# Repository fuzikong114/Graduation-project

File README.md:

# Graduation-project

毕业设计项目的硬件资料。

## 项目列表

| 目录 | 说明 | 状态 |
|---|---|---|
| [`hardware/stm32-environment-monitor`](hardware/stm32-environment-monitor) | **基于 STM32 的多功能环境智能监控系统**：温湿度、光照、RTC、OLED、按键、LED、蜂鸣器、12V 灯带控制，12V 输入板载降压 | V1.2，已提交嘉立创打样 |
| [`hardware/parking-bluepill`](hardware/parking-bluepill) | **4 车位检测板**：Blue Pill 核心板 + 4 个红外反射传感器 + OLED（KiCad 工程） | `main` 为初版；**更新版在分支 [`claude/blissful-cannon-at318t`](../../tree/claude/blissful-cannon-at318t)**（尚未合并） |

## 环境监控板（V1.2）简介

- 主控：立创·地阔星 STM32F103C8T6 开发板，插在 2×20 排母上。
- 传感与显示：GXHT30C 温湿度、SD3077 实时时钟（CR1220 备份电池）、0.96" OLED（4P 母座）、光敏电阻。
- 输出：有源蜂鸣器、红/绿/黄 LED、12V LED 灯带（AO3400A 开关）。
- 输入：4 个按键（PA0~PA3）。
- 供电：12V DC 座 → 保险丝 → XL1509 降压到 5V；3.3V 由开发板 LDO 提供。
- 下载程序：开发板自带 SWD 口，接 DAP-Link；Type-C 只供电。

更多内容（引脚表、BOM、Gerber、装配注意事项）见
[环境监控板 README](hardware/stm32-environment-monitor/README.md)，
原理图见 [`docs/原理图.png`](hardware/stm32-environment-monitor/docs/原理图.png)。

## 车位检测板的更新版

更新版（2026-11-12）在分支 `claude/blissful-cannon-at318t`，`main` 上还是旧版。主要改动：

- 核心板改为 GD32F103C8T6 Type-C 核心板（引脚与 Blue Pill 兼容）。
- 传感器由 VCNT2030 改为 XL-ITR8307（成兴光，现货，引脚外露好焊）。
- 修正 OLED 引脚顺序，加去耦电容和 GND 铺铜，附嘉立创 SMT 的 BOM。
- PCB 文件改为 KiCad 9 格式，方便导入嘉立创 EDA。

详细说明见该分支的 `hardware/parking-bluepill/CHANGES.md`。

## 工具

- 环境监控板：嘉立创 EDA 专业版（`.epro`）
- 车位检测板：KiCad

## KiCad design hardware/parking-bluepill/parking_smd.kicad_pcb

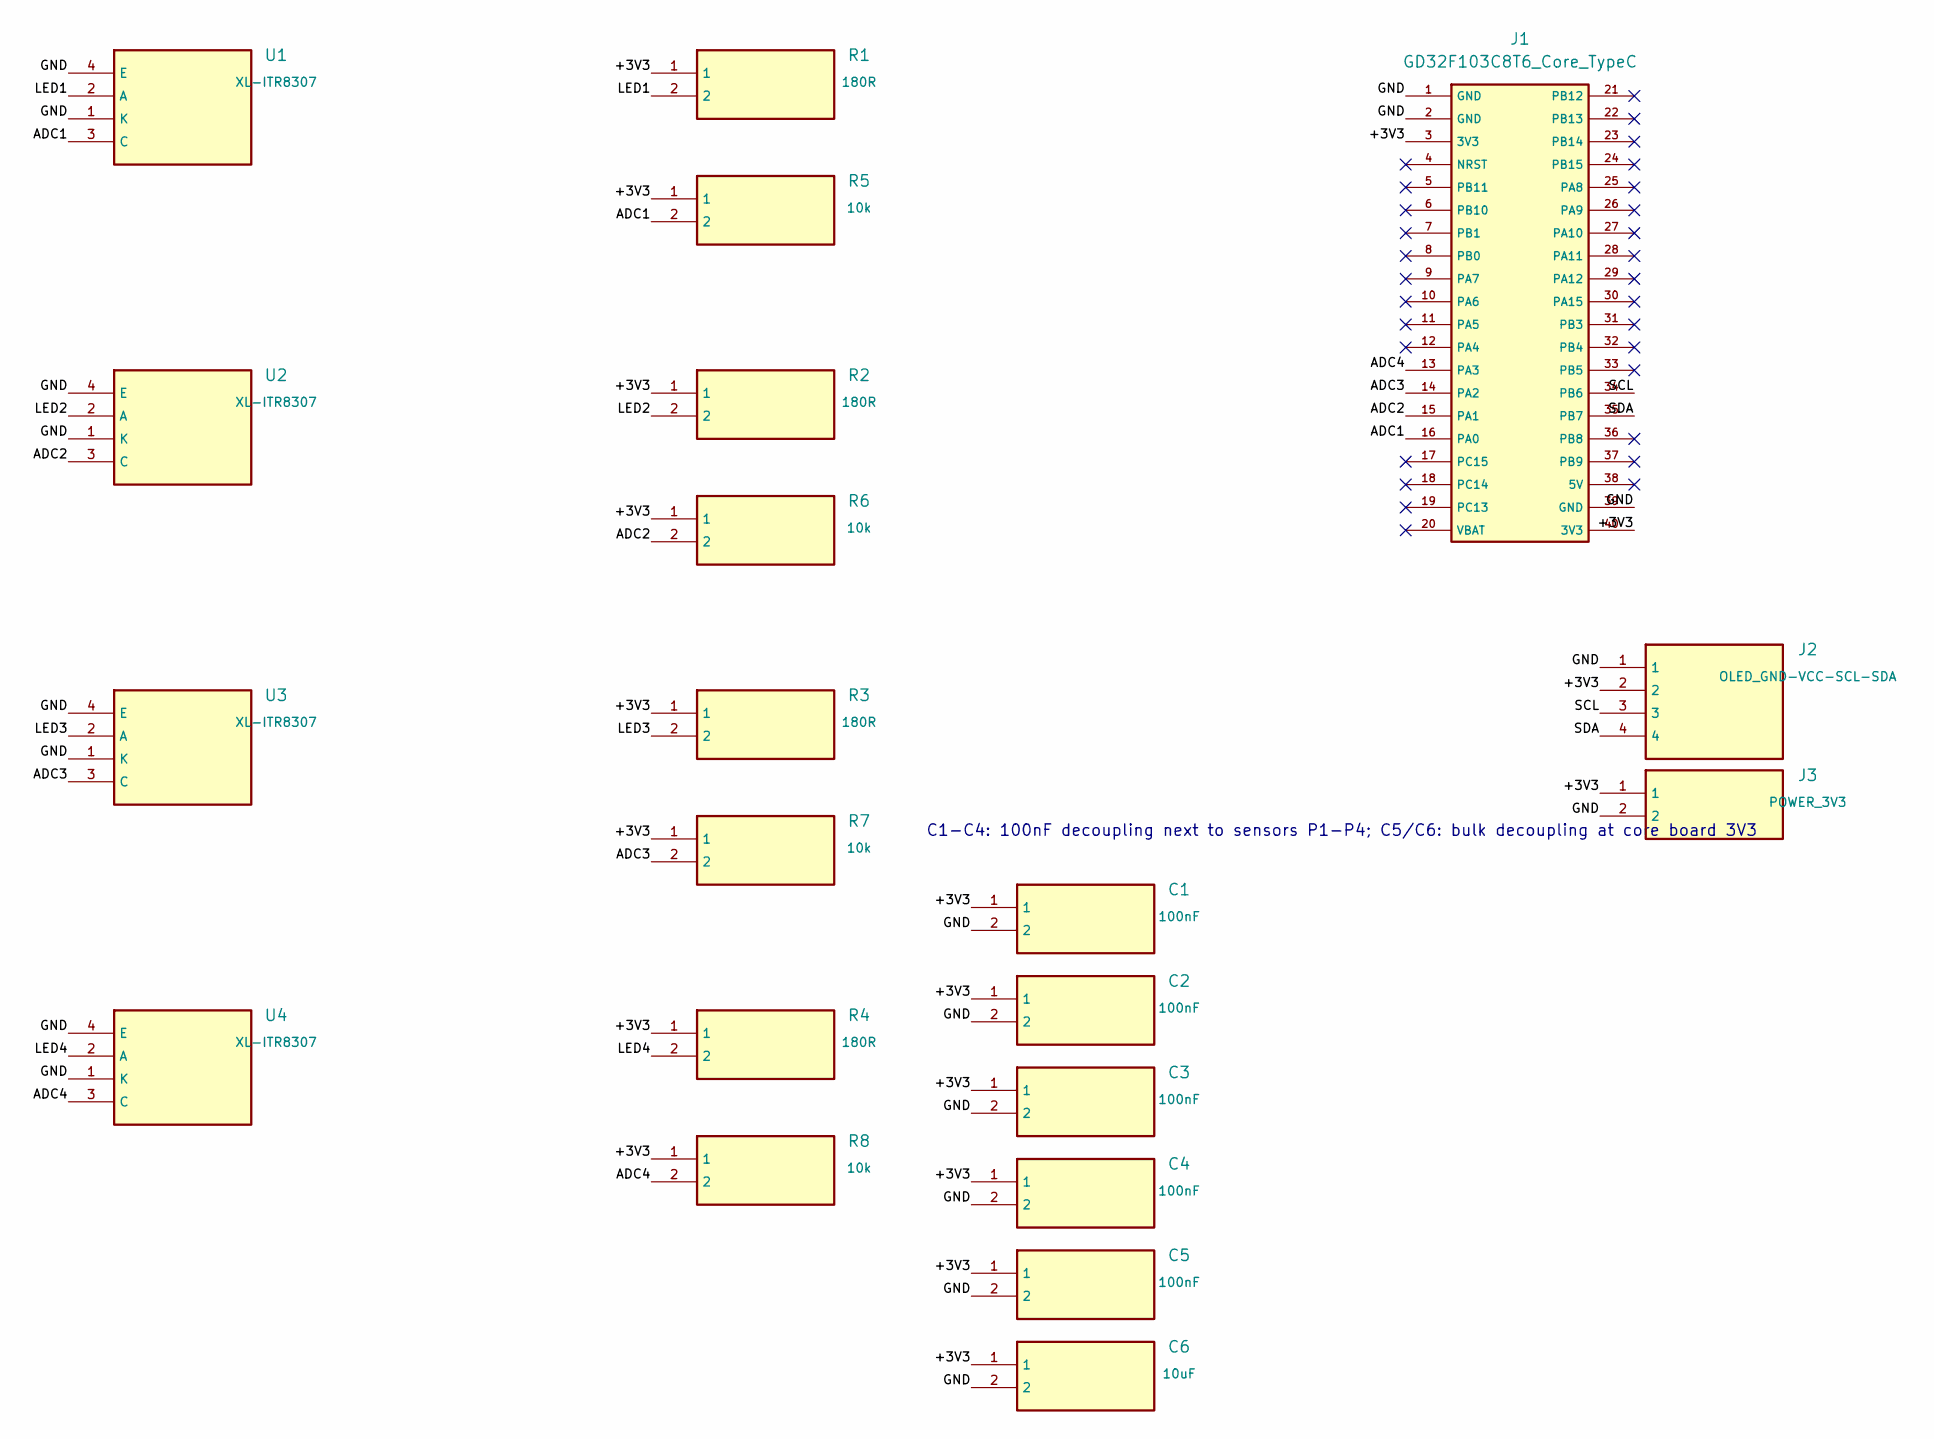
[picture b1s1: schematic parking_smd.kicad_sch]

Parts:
C1, C2, C3, C4, C5: 100nF; C_0805_2012Metric; LCSC C49678
C6: 10uF; C_0805_2012Metric; LCSC C15850
J1: GD32F103C8T6_Core_TypeC; BluePill_2x20_P2.54_Row15.24
J2: OLED_GND-VCC-SCL-SDA; PinHeader_1x04_P2.54mm_Vertical
J3: POWER_3V3; PinHeader_1x02_P2.54mm_Vertical
R1, R2, R3, R4: 180R; R_0805_2012Metric; LCSC C25270
R5, R6, R7, R8: 10k; R_0805_2012Metric; LCSC C17414
U1, U2, U3, U4: XL-ITR8307; ITR8307; LCSC C7545642

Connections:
/+3V3: C1.1, C2.1, C3.1, C4.1, C5.1, C6.1, J1.3 (3V3), J1.40 (3V3), J2.2, J3.1, R1.1, R2.1, R3.1, R4.1, R5.1, R6.1, R7.1, R8.1
/ADC1: J1.16 (PA0), R5.2, U1.3 (C)
/ADC2: J1.15 (PA1), R6.2, U2.3 (C)
/ADC3: J1.14 (PA2), R7.2, U3.3 (C)
/ADC4: J1.13 (PA3), R8.2, U4.3 (C)
/GND: C1.2, C2.2, C3.2, C4.2, C5.2, C6.2, J1.1 (GND), J1.2 (GND), J1.39 (GND), J2.1, J3.2, U1.1 (K), U1.4 (E), U2.1 (K), U2.4 (E), U3.1 (K), U3.4 (E), U4.1 (K), U4.4 (E)
/LED1: R1.2, U1.2 (A)
/LED2: R2.2, U2.2 (A)
/LED3: R3.2, U3.2 (A)
/LED4: R4.2, U4.2 (A)
/SCL: J1.34 (PB6), J2.3
/SDA: J1.35 (PB7), J2.4

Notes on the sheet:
C1-C4: 100nF decoupling next to sensors P1-P4; C5/C6: bulk decoupling at core board 3V3

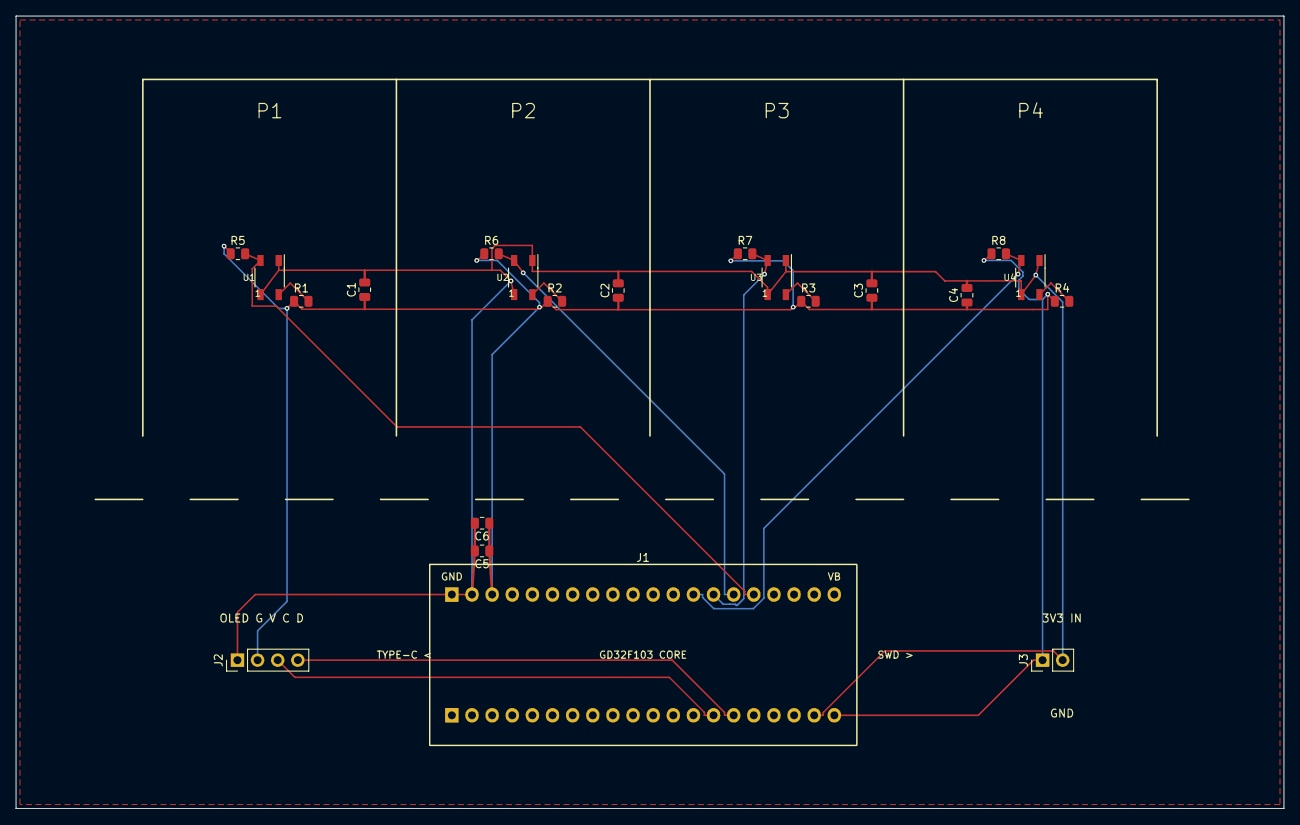
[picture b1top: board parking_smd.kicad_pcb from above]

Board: 2 copper layers, 160.0 x 100.0 mm, 21 parts (0 on the bottom side), 12 nets.

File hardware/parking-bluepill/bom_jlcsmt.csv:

Comment,Designator,Footprint,LCSC Part #
180R,"R1,R2,R3,R4",R_0805_2012Metric,C25270
10k,"R5,R6,R7,R8",R_0805_2012Metric,C17414
100nF,"C1,C2,C3,C4,C5",C_0805_2012Metric,C49678
10uF,C6,C_0805_2012Metric,C15850
XL-ITR8307,"U1,U2,U3,U4",ITR8307,C7545642
